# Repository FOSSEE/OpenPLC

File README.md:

# Introduction

- [Introduction](#introduction)
  - [What is OpenPLC?](#what-is-openplc)
  - [Our story](#our-story)
  - [Our solutions](#our-solutions)
    - [Hardware](#hardware)
    - [Software](#software)
- [Community and contributing](#community-and-contributing)
  - [Forking and cloning](#forking-and-cloning)
- [Directory Structure](#directory-structure)
- [Licence](#licence)

## What is OpenPLC?

OpenPLC is an open source **P**rogrammable **L**ogic **C**ontroller(**PLC**). Our hardware/s are functionally PLCs that can be programmed using [Ladder Logic diagram (LD)](https://en.wikipedia.org/wiki/Ladder_logic), as well as [Function Block diagram (FBD)](https://en.wikipedia.org/wiki/Function_block_diagram). We have designed the systems for academic purpose and to enable effective learning of programming PLCs. For this reason, we are also providing a set of *modules* that supplement the PLCs, which can be used to perform experiments like *simple traffic light, elevator, conveyor belt etc.*

## Our story

Few years ago we came across the need for an affordable and functional PLC for educational purposes. Every year, a large number of students in our colleges are undergoing training in PLCs without proper hands-on experience. The sky-high cost of the setup is a reason, also is the high maintenance because of being used by students. Vendor specific tools and work-flow, which are often complex, is another hindrance.

## Our solutions

### Hardware

OpenPLC consists of **two** versions
- OpenPLC Version 1 : Hardware based on AVR's [**ATmega16A**](https://www.microchip.com/wwwproducts/en/ATmega16A) and programmed using **LD**
- OpenPLC Version 2 : Hardware based on [**Raspberry Pi**](https://www.raspberrypi.org/products/raspberry-pi-zero-w/) and programmed using **FBD**

As mentioned earlier, we are also providing a set of plug-and-play modules for practising a range of experiments. The current ones are
- Elevator/Conveyor belt : Consists of a timing bet, a motor and a motor driver that can be controlled.
- Temperature Sensing and control.
- Switches : an array of *normally-open, normally-closed and latch* switches.
- Simple traffic light.

### Software

The two versions of PLCs uses two different software for programming.

- [LDMicro](Software/OpenPLCV1_LDMicro/) : A simple and intuitive LD programming IDE, used for programming *OpenPLC Version 1*. It is a forked and locally maintained version of [Jonathan Westhues](https://github.com/LDmicro/LDmicro) software.
- [4diac](https://www.eclipse.org/4diac/index.php) : A system, used for *OpenPLC version 2*, that consists of an IDE and a runtime environment for FBD programming and deployment. At present we directly use the [Eclipse 4diac](https://www.eclipse.org/4diac/) project with the Raspberry Pi work-flow.
 
*Note : Detailed documentation regarding each of the above are present in the respective directories.*

___

# Community and contributing

OpenPLC is developed by [FOSSEE](https://fossee.in/) and by users like you. We welcome both pull requests and issues on GitHub. How to and guides pertaining to both *software* and *hardware* can be found in the respective directories.

## Forking and cloning

The repository consists of a few [git submodules](https://git-scm.com/book/en/v2/Git-Tools-Submodules). To clone them along with this repo use the following command.

`git clone --recurse-submodules -j8 https://github.com/FOSSEE/OpenPLC.git'

___

# Directory Structure
      .
      ├── OpenPLC_modules     # OpenPLC modules resources including designs
      ├── OpenPLC_version_1   # OpenPLC version 1 resources including designs
      ├── OpenPLC_version_2   # OpenPLC version 2 resources including designs
      ├── LICENSE             # license
      └── README.md           # this readme

<!-- A Programmable Logic Controller generally has a set of input and output ports to which the external peripherals are connected, which are
to be electrically controlled by the PLC.
Looking into the flow of working with the PLC, the processor tries to make decisions in accordance with the program, generally written by the user using some programming language is used to write the logic and program these units.
Some of the languages commonly used are Function Block Diagram, Ladder Diagram, Structured Text, Sequential Function Chart and Instruction List.

The objective is to create an Open Source PLC, which has the capabilities of an industrial PLC, but at a much affordable and simpler user interface. Currently we have 2 versions

1. Version 1 - It incorporates a development board, that works on AVR’s ATmega16A IC, giving up to 40 pins, most of which can be used and programmed as the Input-Output pins as it’s done on a PLC.
Here the Programming language used here is Ladder Logic which is one of the easiest and also, robust in terms of its efficiency.
The main point here is, this device is a standalone device, which can work without the host system being there, just being powered by a source.
HEX files to be generated according to the controller are generated by a software called __LDMicro__, freely available for Windows and Linux users alike.
The programming on the board is done via an *USB-ASP* device through ISP headers.
All the processor wants now is a code to be dumped on it to start automating your small needs.

2. Version 2 - It uses Function Block(FB) programming language to write the logic. The system is build around a Raspberry Pi Zero, which runs a realtime environment build for IEC61499 standard. The platform we are using is **4diac**, which is implementation of IEC 16499. It has got 2 components :
   * 4diac IDE - the programming interface for writing logics using FBs.
   * FORTE - the runtime present in the actual hardware-- here a Raspberry Pi.

### The Modules

We have developed 4 different modules that goes along with the PLCs for performing experiments; trying various control methods.
   * Motor module - for controlling a motor
   * Temperature Sensing and control
   * Switches - array of various types of switches
   * Traffic light. -->

The OpenPLC setup is shown below:

<!--  -->

___

# Licence

OpenPLC is released under the MIT license. Some part of the software are released under other licences specified.

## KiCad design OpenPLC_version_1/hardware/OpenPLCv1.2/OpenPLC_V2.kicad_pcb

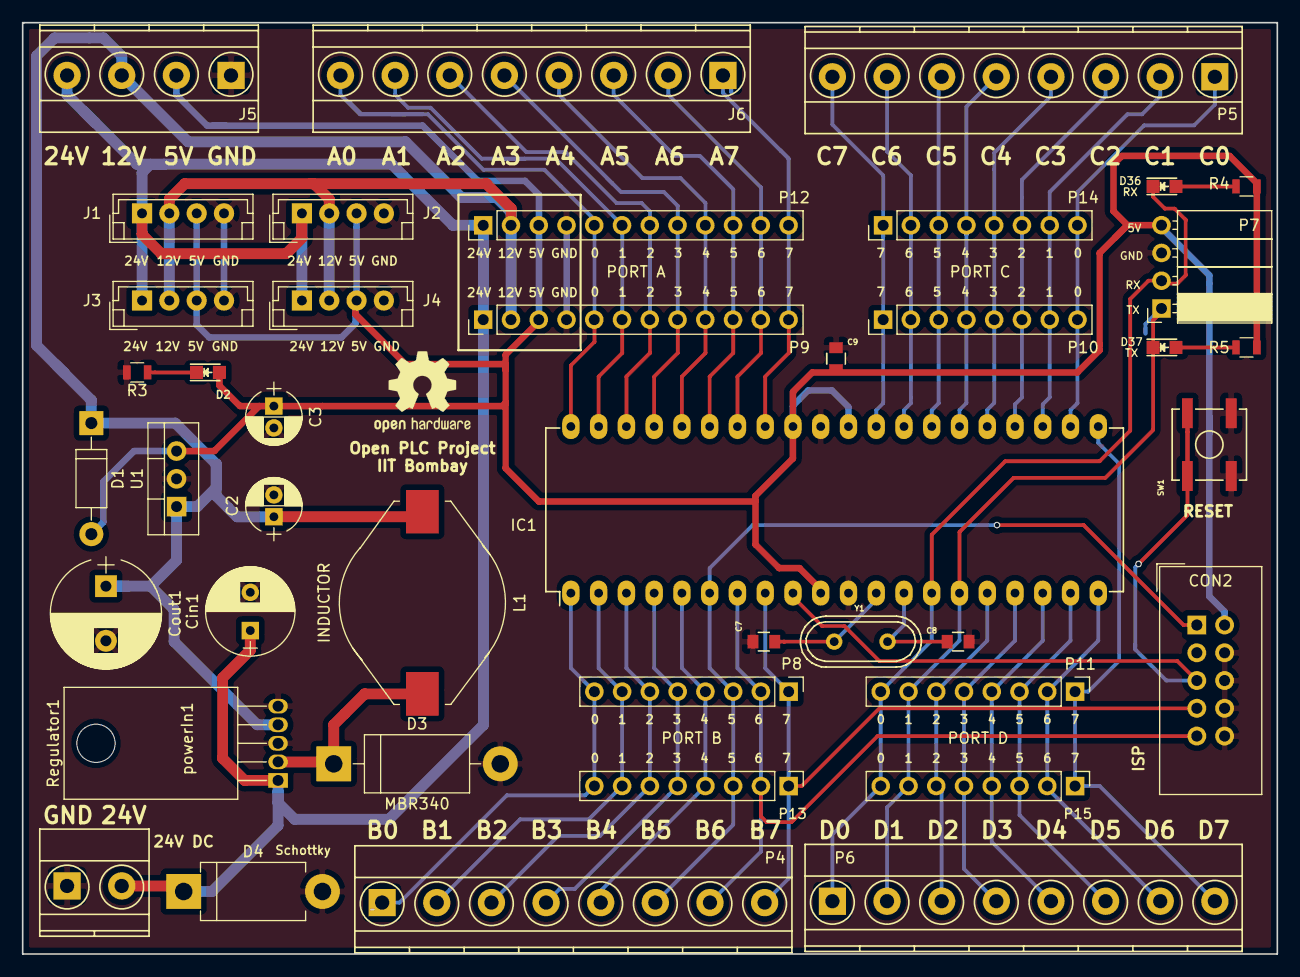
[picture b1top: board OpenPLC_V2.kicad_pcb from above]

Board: 2 copper layers, 114.8 x 85.2 mm, 42 parts (0 on the bottom side), 43 nets.

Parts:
C2: 100uF; CP_Radial_D5.0mm_P2.00mm
C3: 10uF; CP_Radial_D5.0mm_P2.00mm
C7, C8: 22pF; C_0805
C9: 100nF; C_0805
CON2: AVR-ISP-10; IDC-Header_2x05_Pitch2.54mm_Straight
Cin1: 100uf; CP_Radial_D8.0mm_P3.50mm
Cout1: 1000uf; CP_Radial_D10.0mm_P5.00mm
D1: D; D_DO-41_SOD81_P10.16mm_Horizontal
D2: LED; LED_0805
D3: MBR340; D_DO-201AD_P15.24mm_Horizontal
D4: D_Schottky; D_DO-201AD_P12.70mm_Horizontal
D36: RX; LED_0805
D37: TX; LED_0805
IC1: ATMEGA16-P; DIP-40_W15.24mm_LongPads
J1, J2, J3, J4: Conn_01x04; JST_EH_B04B-EH-A_04x2.50mm_Straight
J5: Screw_Terminal_01x04; TerminalBlock_Phoenix_MKDS1.5-4pol
J6: Screw_Terminal_01x08; TerminalBlock_Phoenix_MKDS1.5-8pol
L1: INDUCTOR; L_Fastron_PISR_Handsoldering
P4: PortB; TerminalBlock_Phoenix_MKDS1.5-8pol
P5: PortC; TerminalBlock_Phoenix_MKDS1.5-8pol
P6: PortD; TerminalBlock_Phoenix_MKDS1.5-8pol
P7: Max232; Socket_Strip_Angled_1x04_Pitch2.54mm
P8: PortB_B; Socket_Strip_Straight_1x08_Pitch2.54mm
P9: PortA_B; Socket_Strip_Straight_1x12_Pitch2.54mm
P10: PortC_B; Socket_Strip_Straight_1x08_Pitch2.54mm
P11: PortD_B; Socket_Strip_Straight_1x08_Pitch2.54mm
P12: PortA_M; Pin_Header_Straight_1x12_Pitch2.54mm
P13: PortB_M; Pin_Header_Straight_1x08_Pitch2.54mm
P14: PortC_M; Pin_Header_Straight_1x08_Pitch2.54mm
P15: PortD_M; Pin_Header_Straight_1x08_Pitch2.54mm
R3: 470E; R_0805
R4, R5: 1K; R_0805
Regulator1: 24 to 12; TO-220-5_Horizontal
SW1: SW_PUSH; SW_SPST_B3SL-1002P
U1: 7805; TO-220-3_Vertical
Y1: 16Mhz; Crystal_HC49-U_Vertical
powerIn1: 24V; TerminalBlock_Phoenix_MKDS1.5-2pol

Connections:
5V: C3.1, C9.1, CON2.2, D1.2, D2.2, IC1.10, IC1.30, IC1.32, J1.3, J2.3, J3.3, J4.3, J5.2, P7.4, P9.3, P12.3, R4.2, R5.2, U1.3
12V: C2.1, Cout1.1, D1.1, J1.2, J2.2, J3.2, J4.2, J5.3, L1.2, P9.2, P12.2, Regulator1.4, U1.1
24V: Cin1.1, D4.1, J1.1, J2.1, J3.1, J4.1, J5.4, P9.1, P12.1, Regulator1.1, powerIn1.2
/A0: IC1.40, J6.8, P9.5, P12.5
/A1: IC1.39, J6.7, P9.6, P12.6
/A2: IC1.38, J6.6, P9.7, P12.7
/A3: IC1.37, J6.5, P9.8, P12.8
/A4: IC1.36, J6.4, P9.9, P12.9
/A5: IC1.35, J6.3, P9.10, P12.10
/A6: IC1.34, J6.2, P9.11, P12.11
/A7: IC1.33, J6.1, P9.12, P12.12
/B0: IC1.1, P4.1, P8.8, P13.8
/B1: IC1.2, P4.2, P8.7, P13.7
/B2: IC1.3, P4.3, P8.6, P13.6
/B3: IC1.4, P4.4, P8.5, P13.5
/B4: IC1.5, P4.5, P8.4, P13.4
/C0: IC1.22, P5.1, P10.8, P14.8
/C1: IC1.23, P5.2, P10.7, P14.7
/C2: IC1.24, P5.3, P10.6, P14.6
/C3: IC1.25, P5.4, P10.5, P14.5
/C4: IC1.26, P5.5, P10.4, P14.4
/C5: IC1.27, P5.6, P10.3, P14.3
/C6: IC1.28, P5.7, P10.2, P14.2
/C7: IC1.29, P5.8, P10.1, P14.1
/D2: IC1.16, P6.3, P11.6, P15.6
/D3: IC1.17, P6.4, P11.5, P15.5
/D4: IC1.18, P6.5, P11.4, P15.4
/D5: IC1.19, P6.6, P11.3, P15.3
/D6: IC1.20, P6.7, P11.2, P15.2
/D7: IC1.21, P6.8, P11.1, P15.1
/MISO: CON2.9, IC1.7, P4.7, P8.2, P13.2
/MOSI: CON2.1, IC1.6, P4.6, P8.3, P13.3
/RST: CON2.5, IC1.9, SW1.2
/RX: D36.1, IC1.14, P6.1, P7.2, P11.8, P15.8
/SCK: CON2.7, IC1.8, P4.8, P8.1, P13.1
/TX: D37.1, IC1.15, P6.2, P7.1, P11.7, P15.7
GND: C2.2, C3.2, C7.1, C8.1, C9.2, CON2.4, CON2.6, CON2.8, CON2.10, Cin1.2, Cout1.2, D3.2, D4.2, IC1.11, IC1.31, J1.4, J2.4, J3.4, J4.4, J5.1, P7.3, P9.4, P12.4, R3.2, Regulator1.3, Regulator1.5, SW1.1, U1.2, powerIn1.1
unnamed: C7.2, IC1.12, Y1.1
unnamed: C8.2, IC1.13, Y1.2
unnamed: D2.1, R3.1
unnamed: D3.1, L1.1, Regulator1.2
unnamed: D36.2, R4.1
unnamed: D37.2, R5.1

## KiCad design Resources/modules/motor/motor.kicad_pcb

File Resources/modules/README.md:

# OpenPLC Modules

Addon modules for OpenPLC experiments.
- Traffic light - represent a 3 way traffic light 
- Motor driver for lift - circuit required for driving the motor, receiving and passing on the limit-switch state and as an indicator showing the given logic 
- Heater/temperature control - elements to drive the roister, which also doubles as the heating element, the cooling fan and collecting and passing on thermistor values 
- Switches - an array of a combination of NO, NC and latch switches with indicator LEDs

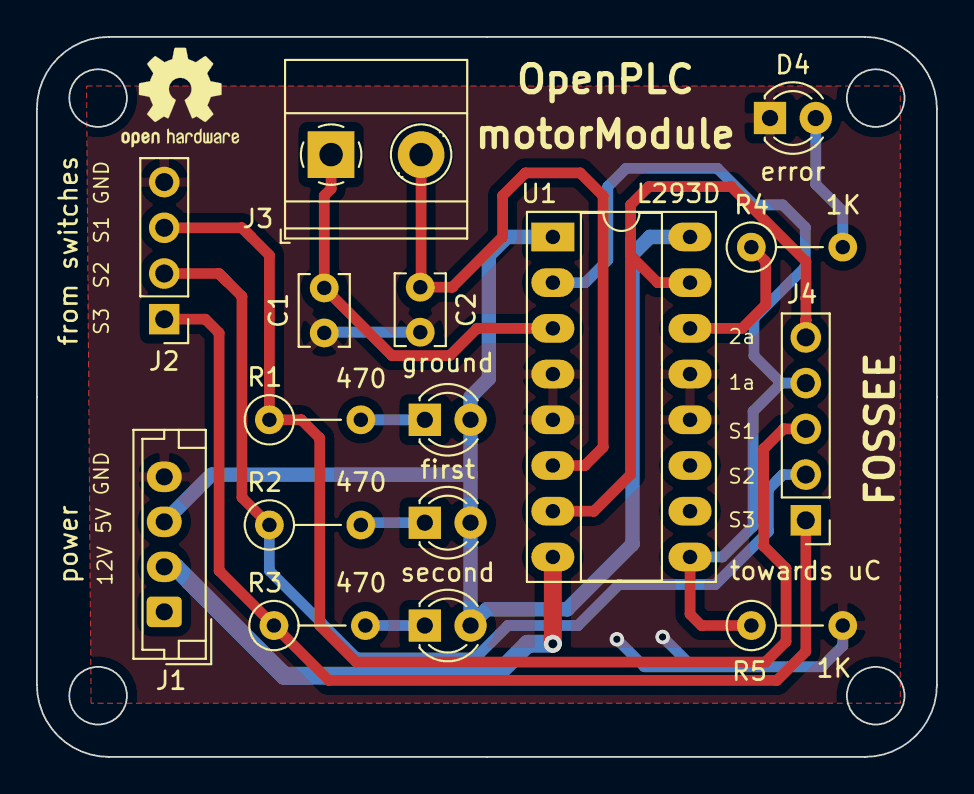
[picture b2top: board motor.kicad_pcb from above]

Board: 2 copper layers, 50.0 x 40.0 mm, 16 parts (0 on the bottom side), 15 nets.

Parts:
C1, C2: 1uf; C_Disc_D3.8mm_W2.6mm_P2.50mm
D4: error; LED_D3.0mm
J1: power; JST_EH_B4B-EH-A_1x04_P2.50mm_Vertical
J2: from switches; PinHeader_1x04_P2.54mm_Vertical
J3: motor; TerminalBlock_Phoenix_MKDS-1,5-2_1x02_P5.00mm_Horizontal
J4: towards uC; PinHeader_1x05_P2.54mm_Vertical
R1, R2, R3: 470; R_Axial_DIN0207_L6.3mm_D2.5mm_P5.08mm_Vertical
R4, R5: 1K; R_Axial_DIN0207_L6.3mm_D2.5mm_P5.08mm_Vertical
U1: L293D; DIP-16_W7.62mm_Socket_LongPads
first: LED; LED_D3.0mm
ground: LED; LED_D3.0mm
second: LED; LED_D3.0mm

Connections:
+5V: J1.3, U1.1, U1.16, first.2, ground.2, second.2
+12V: J1.2, U1.8
/1a: J4.4, R5.1, U1.2, U1.9
/2a: J4.5, U1.7, U1.15
/sw1: J2.3, J4.3, R1.1
/sw2: J2.2, J4.2, R2.1
/sw3: J2.1, J4.1, R3.1
GND: C1.1, C2.2, D4.1, J1.4, J2.4, R5.2, U1.4, U1.5, U1.12, U1.13
unnamed: C1.2, J3.1, U1.3
unnamed: C2.1, J3.2, U1.6
unnamed: R1.2, ground.1
unnamed: R2.2, first.1
unnamed: R3.2, second.1
unnamed: D4.2, R4.2
unnamed: R4.1, U1.14

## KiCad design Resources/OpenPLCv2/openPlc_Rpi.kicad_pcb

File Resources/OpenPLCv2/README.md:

# OpenPLC Version 2

Version 2 is a work in progress and you may follow us [here](https://github.com/VishnuEaswaran/OpenPLC/tree/master/Resources/OpenPLCv2).

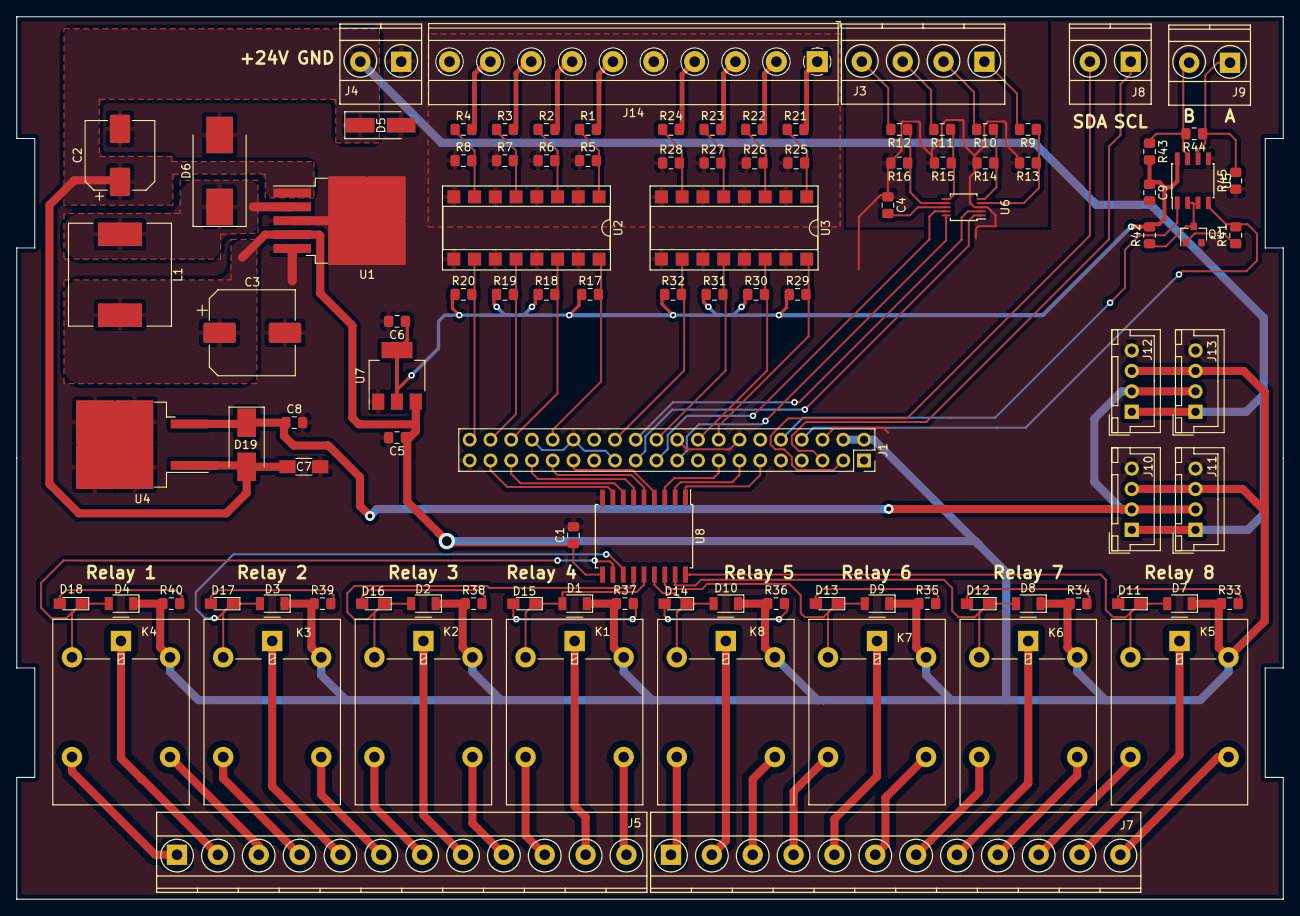
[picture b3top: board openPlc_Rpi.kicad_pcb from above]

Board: 2 copper layers, 155.0 x 108.0 mm, 103 parts (0 on the bottom side), 100 nets.

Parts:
C1: 100nf; C_0805_2012Metric_Pad1.15x1.40mm_HandSolder
C2: 150uf; CP_Elec_8x10
C3: 1000uf; CP_Elec_10x10
C4: 100n; C_0805_2012Metric_Pad1.15x1.40mm_HandSolder
C5, C6, C9: C; C_0805_2012Metric_Pad1.15x1.40mm_HandSolder
C7: Cap_tantalum_1206_3218; C_1206_HandSoldering
C8: .1uf; C_0805_2012Metric_Pad1.15x1.40mm_HandSolder
D1, D2, D3, D4, D7, D8, D9, D10: D_Zener; D_1206
D5: D_Zener; D_SMA_Handsoldering
D6: D_Schottky_power; D_SMC_Handsoldering
D11, D12, D13, D14, D15, D16, D17, D18: LED; LED_0805_HandSoldering
D19: S1BB; D_SMB_Handsoldering
J1: Raspberry_Pi_2_3; Socket_Strip_Straight_2x20_Pitch2.54mm
J3: Screw_Terminal_01x04; TerminalBlock_Phoenix_MKDS1.5-4pol
J4, J8, J9: Screw_Terminal_01x02; TerminalBlock_Phoenix_MKDS1.5-2pol
J5, J7: Screw_Terminal_01x12; TerminalBlock_Phoenix_MKDS1.5-12pol
J10, J11, J12, J13: Conn_01x04; JST_XH_B04B-XH-A_04x2.50mm_Straight
J14: Screw_Terminal_01x10; TerminalBlock_Phoenix_MKDS-1,5-10_1x10_P5.00mm_Horizontal
K1, K2, K3, K4, K5, K6, K7, K8: G5LE-1; Relay_SPDT_OMRON-G5LE-1
L1: 680uh; L_12x12mm_h6mm
Q1: BSS123; SOT-23
R1, R2, R3, R4, R5, R6, R7, R8, R9, R10, R11, R12, R21, R22, R23, R24, R25, R26, R27, R28, R41, R42, R43, R45: 10k; R_0805_2012Metric_Pad1.15x1.40mm_HandSolder
R13, R14, R15, R16: 5k; R_0805_2012Metric_Pad1.15x1.40mm_HandSolder
R17, R18, R19, R20, R29, R30, R31, R32: R; R_0805_2012Metric_Pad1.15x1.40mm_HandSolder
R33, R34, R35, R36, R37, R38, R39, R40: R_US; R_0805_2012Metric_Pad1.15x1.40mm_HandSolder
R44: 120R; R_0805_2012Metric_Pad1.15x1.40mm_HandSolder
U1: power_LM2576; TO-263-5_TabPin3
U2, U3: LTV-847; DIP-16_W7.62mm_SMDSocket_SmallPads
U4: power_L7812_smd; TO-263-2
U5: MAX481E; SOIC-8_3.9x4.9mm_Pitch1.27mm
U6: ADS1018IDGS; TSSOP-10_3x3mm_Pitch0.5mm
U7: AMS1117-3.3; SOT-223-3_TabPin2
U8: ULN2803A; SOIC-18W_7.5x11.6mm_Pitch1.27mm

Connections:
+3V3: C6.1, C9.1, J1.1, J1.17, R17.1, R18.1, R19.1, R20.1, R29.1, R30.1, R31.1, R32.1, R42.2, R43.2, U5.8, U7.2
+5V: C1.1, C3.1, C5.1, D1.1, D2.1, D3.1, D4.1, D7.1, D8.1, D9.1, D10.1, J1.2, J1.4, J10.3, J11.3, J12.3, J13.3, K1.5, K2.5, K3.5, K4.5, K5.5, K6.5, K7.5, K8.5, L1.2, R33.1, R34.1, R35.1, R36.1, R37.1, R38.1, R39.1, R40.1, U1.4, U7.3, U8.10
+12V: C8.1, D19.1, J10.2, J11.2, J12.2, J13.2, U4.3
+24V: C2.1, C7.1, D5.1, D19.2, J4.2, J10.1, J11.1, J12.1, J13.1, U1.1, U4.1
/1: J5.10, K1.3
/2: J5.11, K1.1
/3: J5.12, K1.4
/4: J5.7, K2.3
/5: J5.8, K2.1
/6: J5.9, K2.4
/7: J5.4, K3.3
/8: J5.5, K3.1
/9: J5.6, K3.4
/10: J5.1, K4.3
/11: J5.2, K4.1
/12: J5.3, K4.4
/13: J7.10, K5.3
/14: J7.11, K5.1
/15: J7.12, K5.4
/16: J7.7, K6.3
/17: J7.8, K6.1
/18: J7.9, K6.4
/19: J7.4, K7.3
/20: J7.5, K7.1
/21: J7.6, K7.4
/22: J7.1, K8.3
/23: J7.2, K8.1
/24: J7.3, K8.4
/A: J9.1, R44.1, R45.2, U5.6
/B: J9.2, R43.1, R44.2, U5.7
/DIGND: J14.5, J14.10, R5.1, R6.1, R7.1, R8.1, R25.1, R26.1, R27.1, R28.1, U2.2, U2.4, U2.6, U2.8, U3.2, U3.4, U3.6, U3.8
/RXD: J1.10, U5.1
/TXD: J1.8, R41.2, U5.4
CS0: J1.24, U6.2
DI_0: J1.40, R20.2, U2.10
DI_1: J1.38, R19.2, U2.12
DI_2: J1.36, R18.2, U2.14
DI_3: J1.32, R17.2, U2.16
DI_4: J1.26, R32.2, U3.10
DI_5: J1.22, R31.2, U3.12
DI_6: J1.18, R30.2, U3.14
DI_7: J1.16, R29.2, U3.16
DO_0: J1.37, U8.8
DO_1: J1.35, U8.7
DO_2: J1.33, U8.6
DO_3: J1.31, U8.5
DO_4: J1.29, U8.4
DO_5: J1.15, U8.3
DO_6: J1.13, U8.2
DO_7: J1.11, U8.1
GND: C1.2, C2.2, C3.2, C4.1, C5.2, C6.2, C7.2, C8.2, C9.2, D5.2, D6.2, J1.6, J1.9, J1.14, J1.20, J1.25, J1.30, J1.34, J1.39, J4.1, J10.4, J11.4, J12.4, J13.4, Q1.2, R13.2, R14.2, R15.2, R16.2, R45.1, U1.3, U1.5, U2.9, U2.11, U2.13, U2.15, U3.9, U3.11, U3.13, U3.15, U4.2, U5.5, U6.3, U7.1, U8.9
MISO: J1.21, U6.9
MOSI: J1.19, U6.10
unnamed: C4.2, U6.8
unnamed: D1.2, D15.1, K1.2, U8.14
unnamed: D6.1, L1.1, U1.2
unnamed: D10.2, D14.1, K8.2, U8.15
unnamed: D7.2, D11.1, K5.2, U8.18
unnamed: D11.2, R33.2
unnamed: D8.2, D12.1, K6.2, U8.17
unnamed: D12.2, R34.2
unnamed: D9.2, D13.1, K7.2, U8.16
unnamed: D13.2, R35.2
unnamed: D14.2, R36.2
unnamed: D15.2, R37.2
unnamed: D2.2, D16.1, K2.2, U8.13
unnamed: D16.2, R38.2
unnamed: D3.2, D17.1, K3.2, U8.12
unnamed: D17.2, R39.2
unnamed: D4.2, D18.1, K4.2, U8.11
unnamed: D18.2, R40.2
unnamed: J3.1, R9.2
unnamed: J3.2, R10.2
unnamed: J3.3, R11.2
unnamed: J3.4, R12.2
unnamed: J14.1, R21.2
unnamed: J14.2, R22.2
unnamed: J14.3, R23.2
unnamed: J14.4, R24.2
unnamed: J14.6, R1.2
unnamed: J14.7, R2.2
unnamed: J14.8, R3.2
unnamed: J14.9, R4.2
unnamed: Q1.1, R41.1
unnamed: Q1.3, R42.1, U5.2, U5.3
unnamed: R1.1, R5.2, U2.1
unnamed: R2.1, R6.2, U2.3
unnamed: R3.1, R7.2, U2.5
unnamed: R4.1, R8.2, U2.7
unnamed: R10.1, R14.1, U6.5
unnamed: R11.1, R15.1, U6.6
unnamed: R12.1, R16.1, U6.7
unnamed: R9.1, R13.1, U6.4
unnamed: R21.1, R25.2, U3.1
unnamed: R22.1, R26.2, U3.3
unnamed: R23.1, R27.2, U3.5
unnamed: R24.1, R28.2, U3.7
SCK: J1.23, U6.1
SCL: J1.5, J8.1
SDA: J1.3, J8.2

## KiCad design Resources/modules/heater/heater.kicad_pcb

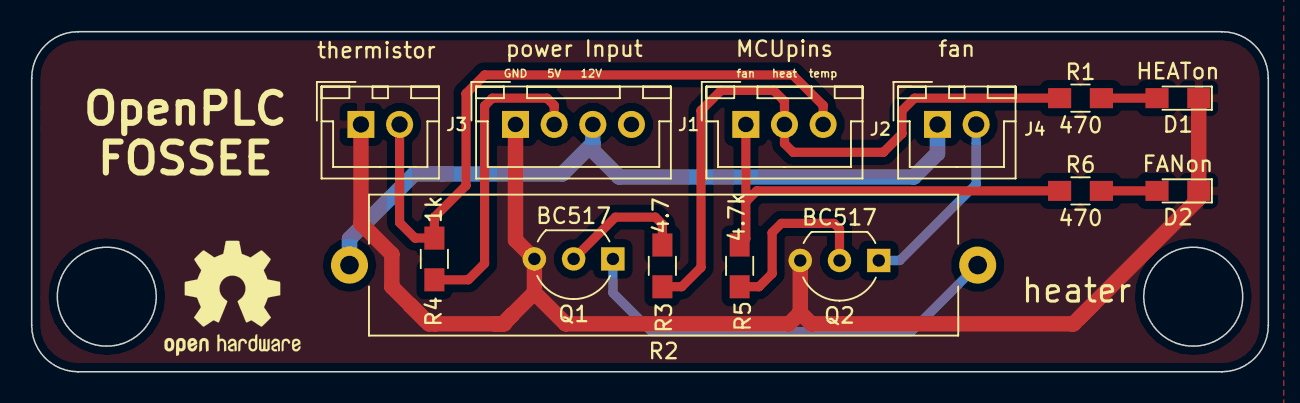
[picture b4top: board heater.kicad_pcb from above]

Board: 2 copper layers, 80.0 x 22.0 mm, 14 parts (0 on the bottom side), 12 nets.

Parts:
D1: HEATon; LED_0805_HandSoldering
D2: FANon; LED_0805_HandSoldering
J1: power Input; JST_XH_B04B-XH-A_04x2.50mm_Straight
J2: MCUpins; JST_XH_B03B-XH-A_03x2.50mm_Straight
J3: thermistor; JST_XH_B02B-XH-A_02x2.50mm_Straight
J4: fan; JST_XH_B02B-XH-A_02x2.50mm_Straight
Q1, Q2: BC517; TO-92_Inline_Wide
R1, R6: 470; R_0805_HandSoldering
R2: 27; R_Axial_Power_L38.0mm_W9.0mm_P40.64mm
R3: 4.7; R_0805_HandSoldering
R4: 1k; R_0805_HandSoldering
R5: 4.7k; R_0805_HandSoldering

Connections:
+5V: J1.2, R4.1
+12V: J1.3, J4.1, R2.2
/fromMcuF: J2.1, R5.2, R6.1
/fromMcuR: J2.2, R1.1, R3.2
/toMcu: J2.3, J3.2, R4.2
GND: D1.1, D2.1, J1.1, J3.1, Q1.3, Q2.3
unnamed: D1.2, R1.2
unnamed: D2.2, R6.2
unnamed: J4.2, Q2.1
unnamed: Q1.1, R2.1
unnamed: Q1.2, R3.1
unnamed: Q2.2, R5.1

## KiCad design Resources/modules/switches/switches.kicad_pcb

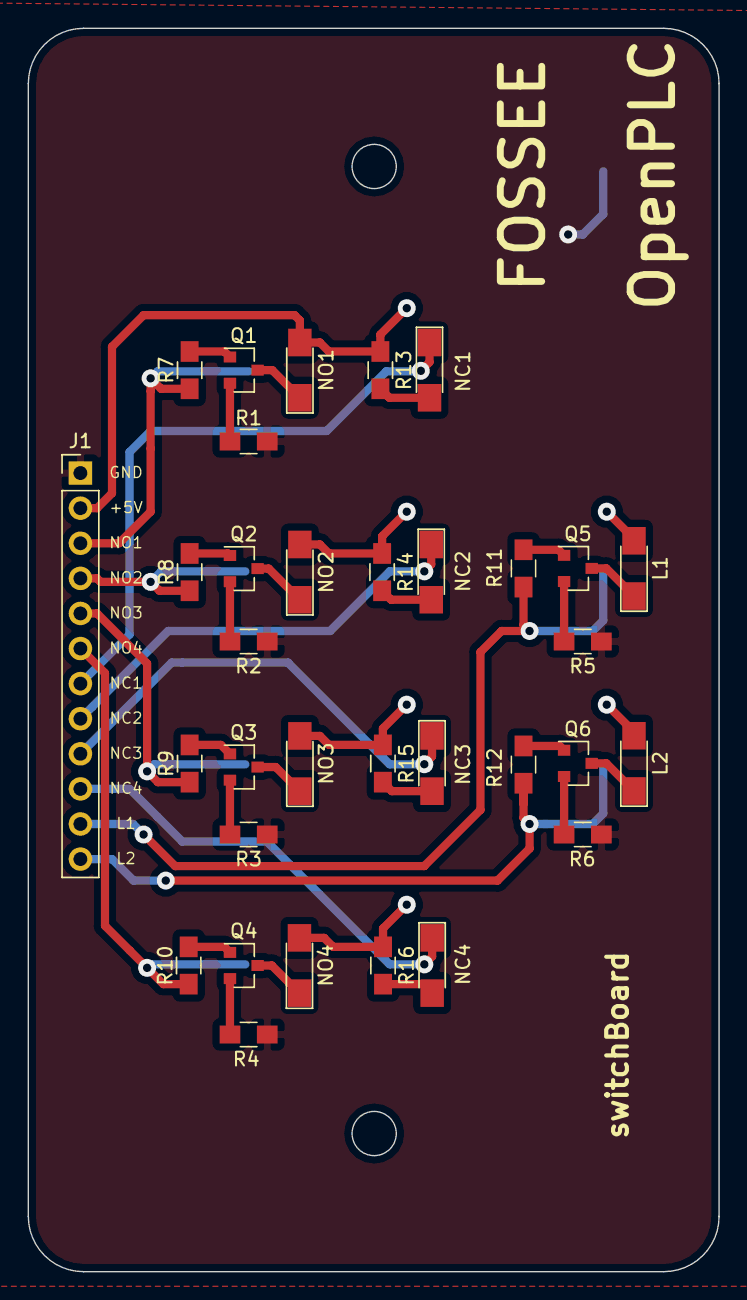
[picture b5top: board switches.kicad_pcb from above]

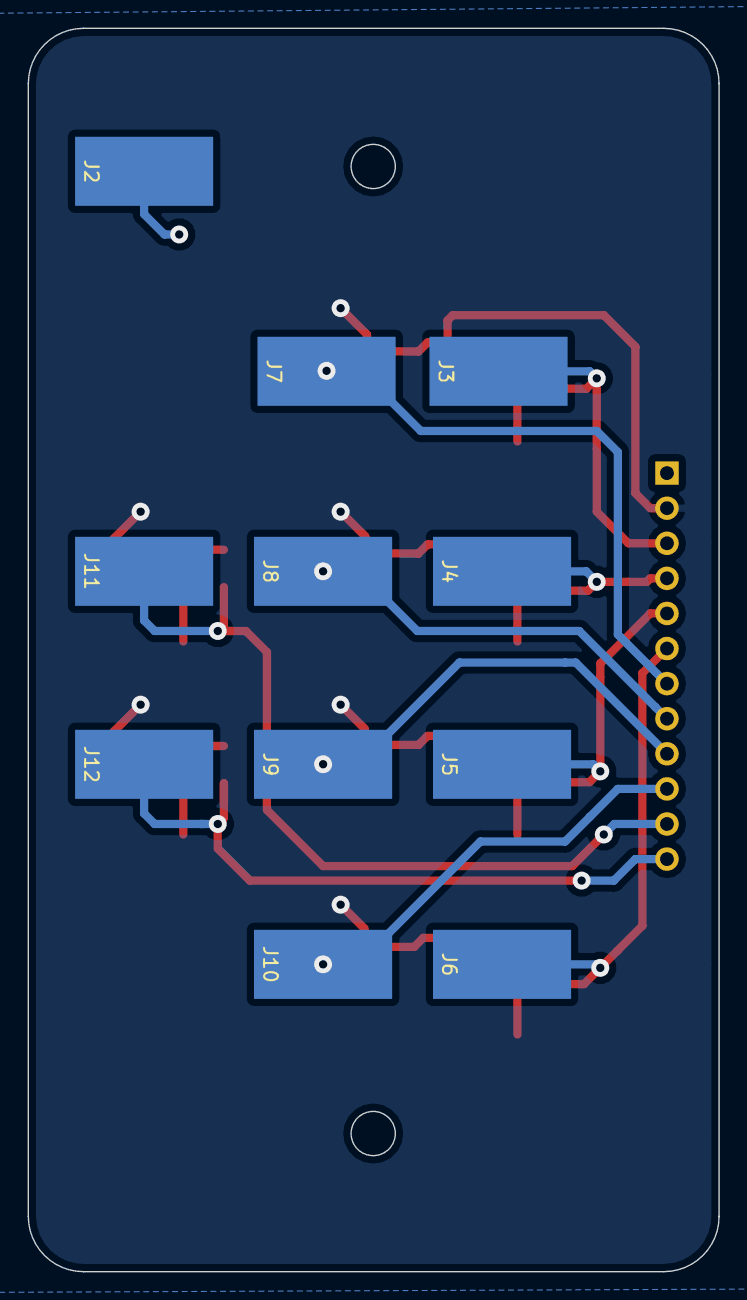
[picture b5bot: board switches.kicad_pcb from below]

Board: 2 copper layers, 50.0 x 90.0 mm, 44 parts (11 on the bottom side), 34 nets.

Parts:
D1: NO1; LED_1206_HandSoldering
D2: NO2; LED_1206_HandSoldering
D3: NO3; LED_1206_HandSoldering
D4: NO4; LED_1206_HandSoldering
D5: L1; LED_1206_HandSoldering
D6: L2; LED_1206_HandSoldering
D7: NC1; LED_1206_HandSoldering
D8: NC2; LED_1206_HandSoldering
D9: NC3; LED_1206_HandSoldering
D10: NC4; LED_1206_HandSoldering
J1: switchesOut; Socket_Strip_Straight_1x12_Pitch2.54mm
J2, J3, J4, J5, J6, J7, J8, J9, J10, J11, J12: Conn_01x01_Female; SolderWirePad_single_SMD_5x10mm
Q1, Q2, Q3, Q4, Q5, Q6: 2N7002; SOT-23
R1, R2, R3, R4, R5, R6, R7, R8, R9, R10, R11, R12, R13, R14, R15, R16: R_US; R_0805_HandSoldering

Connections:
+5V: D1.2, D2.2, D3.2, D4.2, D5.2, D6.2, J1.2, R13.1, R14.1, R15.1, R16.1
/s1: J1.3, J3.1, R7.1
/s2: J1.4, J4.1, R8.1
/s3: J1.5, J5.1, R9.1
/s4: J1.6, J6.1, R10.1
/s5: D7.1, J1.7, J7.1
/s6: D8.1, J1.8, J8.1
/s7: D9.1, J1.9, J9.1
/s8: D10.1, J1.10, J10.1
/s9: J1.11, J11.1, R11.1
/s10: J1.12, J12.1, R12.1
GND: J1.1, J2.1, R1.2, R2.2, R3.2, R4.2, R5.2, R6.2
unnamed: D1.1, Q1.3
unnamed: D2.1, Q2.3
unnamed: D3.1, Q3.3
unnamed: D4.1, Q4.3
unnamed: D5.1, Q5.3
unnamed: D6.1, Q6.3
unnamed: D7.2, R13.2
unnamed: D8.2, R14.2
unnamed: D9.2, R15.2
unnamed: D10.2, R16.2
unnamed: Q1.1, R7.2
unnamed: Q1.2, R1.1
unnamed: Q2.1, R8.2
unnamed: Q2.2, R2.1
unnamed: Q3.1, R9.2
unnamed: Q3.2, R3.1
unnamed: Q4.1, R10.2
unnamed: Q4.2, R4.1
unnamed: Q5.1, R11.2
unnamed: Q5.2, R5.1
unnamed: Q6.1, R12.2
unnamed: Q6.2, R6.1

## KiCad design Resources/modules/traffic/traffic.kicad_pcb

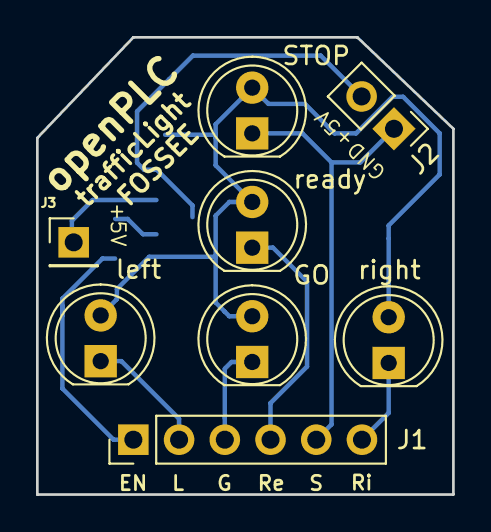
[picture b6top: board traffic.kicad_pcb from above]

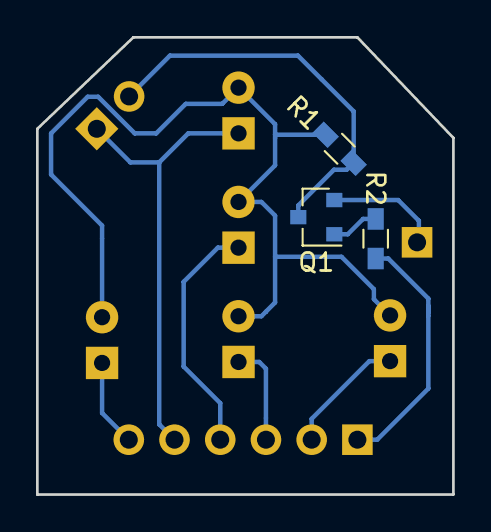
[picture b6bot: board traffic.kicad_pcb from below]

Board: 2 copper layers, 23.1 x 25.4 mm, 11 parts (3 on the bottom side), 10 nets.

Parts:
D1: left; LED_D5.0mm
D2: GO; LED_D5.0mm
D3: right; LED_D5.0mm
D4: ready; LED_D5.0mm
D5: STOP; LED_D5.0mm
J1: Conn_01x06_Male; Socket_Strip_Straight_1x06_Pitch2.54mm
J2: Conn_01x02_Male; Socket_Strip_Straight_1x02_Pitch2.54mm
J3: Conn_01x01_Male; Socket_Strip_Straight_1x01_Pitch2.54mm
Q1: MMBT3906; SOT-23
R1, R2: R; R_0603_HandSoldering

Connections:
+5C: J3.1, Q1.2
unnamed: D1.1, J1.2
unnamed: D1.2, D2.2, D3.2, D4.2, D5.2, R1.1
unnamed: D2.1, J1.3
unnamed: D3.1, J1.6
unnamed: D4.1, J1.4
unnamed: D5.1, J1.5, J2.1
unnamed: J1.1, R2.2
unnamed: J2.2, Q1.3, R1.2
unnamed: Q1.1, R2.1

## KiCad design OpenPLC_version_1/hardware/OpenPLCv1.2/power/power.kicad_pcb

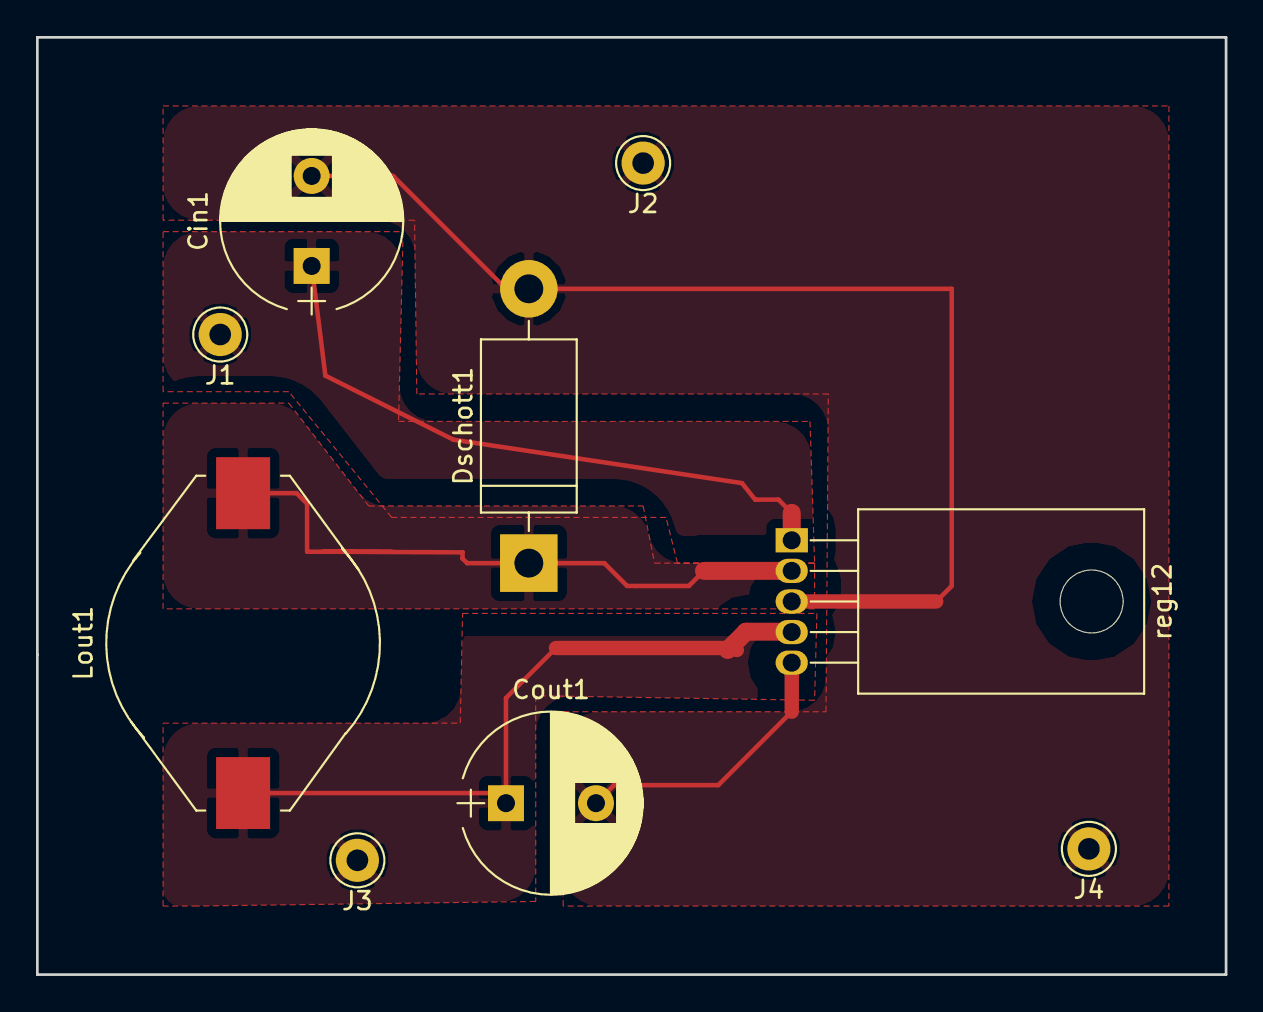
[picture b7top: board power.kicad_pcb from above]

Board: 2 copper layers, 66.0 x 52.1 mm, 9 parts (0 on the bottom side), 4 nets.

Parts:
Cin1: 100uf; CP_Radial_D10.0mm_P5.00mm
Cout1: 1000uf; CP_Radial_D10.0mm_P5.00mm
Dschott1: MBR340; D_DO-201AD_P15.24mm_Horizontal
J1, J2, J3, J4: Conn_01x01_Male; Pin_d1.0mm_L10.0mm_LooseFit
Lout1: H220; L_Fastron_PISR_Handsoldering
reg12: LM2576T-12; TO-220-5_Horizontal

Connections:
GND: Cin1.2, Cout1.2, Dschott1.2, J2.1, J4.1, reg12.3, reg12.5
unnamed: Cin1.1, J1.1, reg12.1
unnamed: Cout1.1, J3.1, Lout1.2, reg12.4
unnamed: Dschott1.1, Lout1.1, reg12.2

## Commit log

2016-04-19 added first ladder file. More to come
2016-04-19 added new ladder file
2016-04-19 added new file for motor
2016-04-19 added new file for LED
2016-04-19 added chapter for motor
2016-04-21 Added software requirements
2016-04-21 Adding Ladder making file
2016-04-21 adding image file
2016-04-21 Changed image file
2016-04-22 done some modifications on images
2016-04-22 Modified image file
2016-04-22 Modified image path in rst file
2016-04-22 modified image path
2016-04-22 added more images
2016-04-22 edited document
2016-04-22 scled an image
2016-04-22 scled all images
2016-04-22 added fuse settings images
2016-04-22 Added new programming document
2016-04-22 edited the document
2016-04-22 adding Readme file
2016-04-22 Edited Readme file
2016-04-22 adding experiments folder
2016-04-22 making some changes
2016-04-22 few files were deleted
2016-04-22 changed readme file
2016-04-22 added README for software used in OpenPLC
2016-04-25 added executable for ldmicro
2016-04-25 changed path for image
2016-04-25 made some changes on scaling image
2016-04-25 Made some re-arrangements
2016-04-25 image paths are changed
2016-04-26 Removed unnecessary files
2016-04-26 Final Cleaning of unnecessary files
2017-04-01 KiCAD Files
2017-04-03 Open_PLC_Modular KiCAD Files
2017-04-04 Folder Hierarchy
2017-04-04 OpenPLC_RS232_Board
2017-04-05 Updated Libraries
2017-04-05 Deleted versioning
2017-04-05 Removed differential pair and improved version compatibility
2017-04-05 Added Gerber files
2017-04-25 Moved files from Documentation to Resources folder
2017-04-25 Modified Main Readme File
2017-04-25 Added Documentation Folder
2017-04-25 Made changes in the Programming-OpenPLC.rst
2017-04-25 Embedding Images to the Documentation files
2017-04-25 Test
2017-04-25 Made Changes in the documentation of Software-Requirements file
2017-04-25 Made Changes in the documentation of Creating-Ladders file
2017-04-26 Changed links and images in Documentation
2017-04-26 Added links for avrdude downloads
2018-04-19 Cleaned pu the traces, removed the fuses, made onboard power management
2018-08-31 Gtk software
2019-01-28 versioning and finalised V 1.3
2019-01-30 directory reorganising
2019-01-30 Gtk Software updates
2019-02-26 added the entire modules devoloped
2019-03-04 altered switches-board design; shifted resistor
2019-03-18 Updated Version two hardware and software descriptions
2019-03-18 typo is->are
2019-03-20 label correction&additions in traffic&switches modules. Updated gerbers - both V1 and modules
2019-03-20 zipped v1.2 gerber and added image
2019-04-09 corrected the gerber file
2019-05-09 added V2 design files + firmware til now; added .gitignore
2019-07-19 unknown changes!
2019-08-22 Added .gitignore file.
2019-08-22 Motor module: grounded 'EN3,4'; terminal connector footprint corrected; 'error led' changed to 3mm; proper footprints for 'switches' and 'towards uC' connectors; proper labelling; added 'designed usi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
2019-09-13 Svg Images for Toolbars in LDmicro
2019-09-13 logo svg
2019-09-13 Acrylic Designs
2019-10-07 new branch and README updated
2019-10-07 added missing image
2019-10-07 replaced the image
2019-11-27 updated README.
2019-12-16 Latest Qt and Gtk Releases for LDmicro
2019-12-16 Legacy Package for Qt
2019-12-17 Primary Gtk Versions
2020-05-14 [vishnu] Started modifying README for better documentation and community engagement.
2020-05-14 [vishnu] Added LICENSE; MIT.
2020-05-14 [vishnu] Added "Directory structure" and LICENSE info.
2020-05-14 [vishnu] Corrected few typos in README. Renamed a few images folders to "assets" and made corresponding changes in thr READMEs.
2020-05-14 [vishnu] Replaced modules and OpenPLCv2 with gitmodules.
2020-05-14 [vishnu] Added gitmodules cloning instructions in README. Renamed subdirectories if Software to sensible ones, UPdated the same change in README.
2020-05-14 [vishnu] Corrected the repo cloning URI
2020-05-14 [vishnu] Corrected ATmega16A hyperlink. Tidied up README with Horizontal rules.
2020-05-14 [vishnu] Hyperlinks for the softwares and added Contributors names to LICENSE.
2020-05-14 [vishnu] Reorganised and tidied OpenPLCv1 folder
2020-05-15 [vishnu] configured branches of submodules
2020-05-15 [vishnu] Moved OpenPLCv2 branch to "working".
2020-05-18 [vishnu] Added openplcv2 submodule and set master as the default branch
2020-05-18 [vishnu] added openplc_modules as submodules
2020-05-19 [vishnu] moved experiments, images, documentation, Designs to respective new folders
2020-05-19 [vishnu] moved v1&2 software subfolders from Software to respective new directories
2020-05-19 [vishnu] removed the submodules. Moved v1 hardware design to new directory.
2020-05-19 [vishnu] added modules submodule and renamed Designs to CAD_designs
2020-05-19 [vishnu] moved LD example files to v1 directory
2020-05-19 [vishnu] corrected README for new directory structure
2020-05-19 [vishnu] Corrected few internal .rst documents and renaed Images->assets within v1 folder
2020-05-19 [vishnu] added LDgtk and LDqt to v1 software suite
2020-05-19 [vishnu] added logo to README
2020-09-02 [vishnu] delete the html file in V1.1
    Deleted unwanted bom artifacts from the source-code
2020-09-15 [vishnu] Updated to the latest commit in modules/hardware submodule.
2020-09-15 [vishnu] Corrected the git repo URI to fossee link.
2022-05-30 changed directory names
2022-05-30 moved module directory
2022-05-31 Added Gerber_Files_OpenPLC_ATmega16.zip
